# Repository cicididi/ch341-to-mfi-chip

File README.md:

# ch341-to-mfi-chip

A CH341F to MFI337/341/343 board.

Tested works.

Check release. Pick the one fits you best from releases and make it.

Usage: [xcertplay](https://github.com/shilapi/xcertplay)

## Todo

Some crazy SKUs.

- [x] USBA-3.3v-CH341-MFI337 (tested, worked)
- [ ] USBC-3.3v-CH341-MFI337
- [ ] USBC-5v-CH341-MFI337
- [x] USBA-5v-CH341-MFI337 (not tested)
- [ ] USBA-3.3v-CH341-MFI343
- [ ] USBC-3.3v-CH341-MFI343
- [ ] USBA-5v-CH341-MFI343
- [ ] USBC-5v-CH341-MFI343
- [ ] USBA-3.3v-CH341-MFI341
- [ ] USBC-3.3v-CH341-MFI341
- [ ] USBA-5v-CH341-MFI341
- [ ] USBC-5v-CH341-MFI341

## Some crezy thing is also happening here

### The Ultra nano version of USBA-5v-CH341-MFI337

|      |      |
|------|------|
|| |

## Build

Check [production](production) for BOM and GERBER file.

## BOM

| No. | Model | Qty |
| ---: | --- | ---: |
| 1 | 10uF 0402 | 2 |
| 2 | 0.1uF 0402 | 3 |
| 3 | USB-212-BCW | 1 |
| 4 | 2kΩ 0402 | 1 |
| 5 | 2.2kΩ 0402 | 2 |
| 6 | 4.7kΩ 0402 | 1 |
| 7 | CH341F | 1 |
| 8 | HR1117V-3.3 | 1 |
| 9 | MFI337S3959 | 1 |

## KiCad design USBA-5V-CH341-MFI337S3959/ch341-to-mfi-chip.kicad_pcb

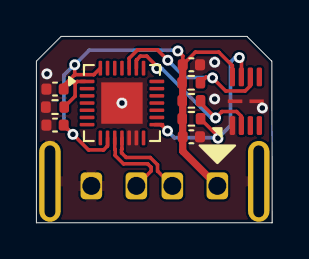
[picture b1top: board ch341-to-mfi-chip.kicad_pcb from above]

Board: 2 copper layers, 13.1 x 10.3 mm, 11 parts (0 on the bottom side), 8 nets.

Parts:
C1: 10uF; C_0402_1005Metric
C3, C4, C5: 0.1uF; C_0402_1005Metric
J1: 917-511A1015B20200
R1: 2k; R_0402_1005Metric
R2, R3: 2.2k; R_0402_1005Metric
R4: 4.7k; R_0402_1005Metric
U1: CH341F; QFN-28-1EP_4x4mm_P0.4mm_EP2.3x2.3mm
U3: MFI337S3959; USON-8_2.5X2.5X0.5P

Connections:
+5V: C1.1, C3.1, C4.1, C5.2, J1.1 (VBUS), R2.1, R3.1, R4.1, U1.9 (V3), U1.28 (VCC), U3.8 (VCC)
/USB_D+: J1.3 (D+), U1.10 (UD+)
/USB_D-: J1.2 (D-), U1.11 (UD-)
GND: C1.2, C3.2, C4.2, C5.1, J1.4 (GND), J1.SH (Shield), R1.2, U1.12 (GND), U1.13 (XI), U1.29 (GND), U3.1 (GND), U3.9 (EP)
unnamed: R1.1, U1.1 (ACT#)
unnamed: R4.2, U1.15 (CS0), U3.7 (RST)
unnamed: R3.2, U1.24 (SCL), U3.6 (SCL)
unnamed: R2.2, U1.23 (SDA), U3.2 (SDA)

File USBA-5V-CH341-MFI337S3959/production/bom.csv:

Designator,Footprint,Quantity,Value,LCSC Part #
C1,0402,1,10uF,
"C3, C4, C5",0402,3,0.1uF,
J1,917-511A1015B20200,1,917-511A1015B20200,
R1,0402,1,2k,
"R2, R3",0402,2,2.2k,
R4,0402,1,4.7k,
U1,QFN-28-1EP_4x4mm_P0.4mm_EP2.3x2.3mm,1,CH341F,
U3,USON-8_2.5X2.5X0.5P,1,MFI337S3959,
